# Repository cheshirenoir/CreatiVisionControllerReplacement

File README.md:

# CreatiVisionControllerReplacement

A bunch of PCBs designed to allow you to replace your failing CreatiVision controller membranes
The 4 sections are designed to be joined with short lengths of patch wire (ribbon cable).
See https://ilike8bits.com/total-joystick-madness/ for a build guide.

Notes: Use 0.6mm PCBs when yuou order. You'll need 3 different PCBs.

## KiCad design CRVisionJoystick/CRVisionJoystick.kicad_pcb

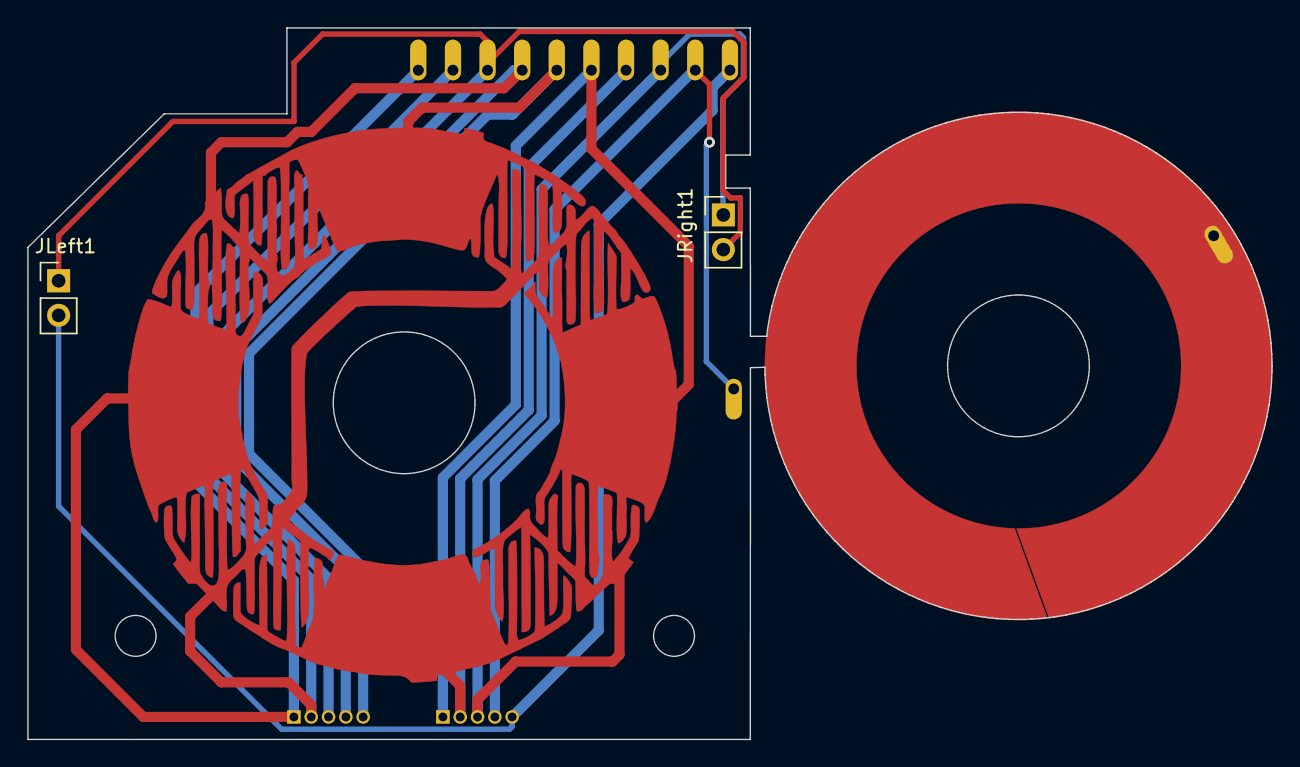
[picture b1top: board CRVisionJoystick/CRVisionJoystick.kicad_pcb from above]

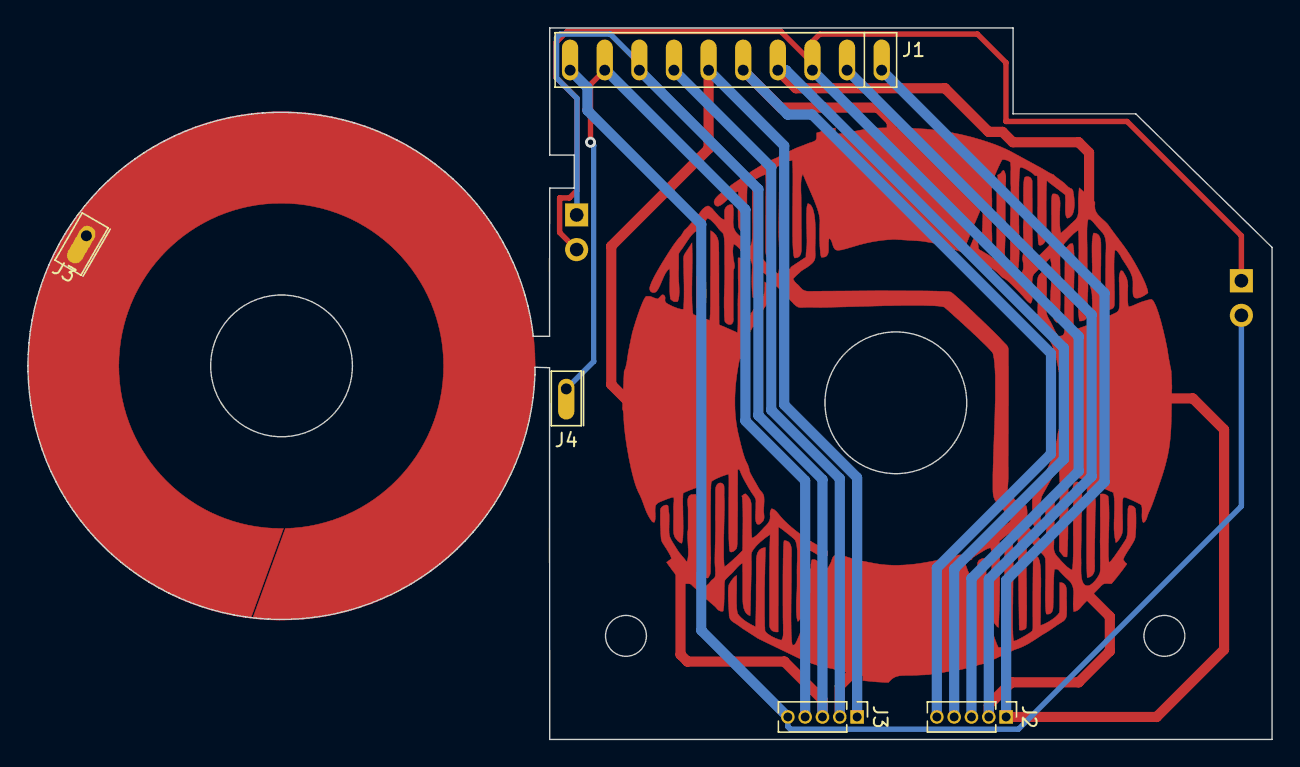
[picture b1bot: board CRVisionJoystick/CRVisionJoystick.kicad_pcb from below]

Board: 2 copper layers, 91.3 x 52.2 mm, 7 parts (5 on the bottom side), 10 nets.

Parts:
J1: Conn_01x10_Female; SIP-10L
J2, J3#2: Conn_01x05_Female; PinHeader_1x05_P1.27mm_Vertical
J3: Signal; SIP-1
J4: Conn_01x01_Female; SIP-1
JLeft1: Conn_01x02_Female; PinHeader_1x02_P2.54mm_Vertical
JRight1: Conn_01x02_Female; PinHeader_1x02_P2.54mm_Vertical

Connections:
unnamed: J1.1, J2.1, J3.1
unnamed: J1.2, J2.2
unnamed: J1.3, J2.3, JLeft1.1, JRight1.2
unnamed: J1.4, J2.4
unnamed: J1.5, J2.5
unnamed: J1.6, J3#2.1
unnamed: J1.7, J3#2.2
unnamed: J1.8, J3#2.3, JRight1.1
unnamed: J1.9, J3#2.4, J4.1
unnamed: J1.10, J3#2.5, JLeft1.2

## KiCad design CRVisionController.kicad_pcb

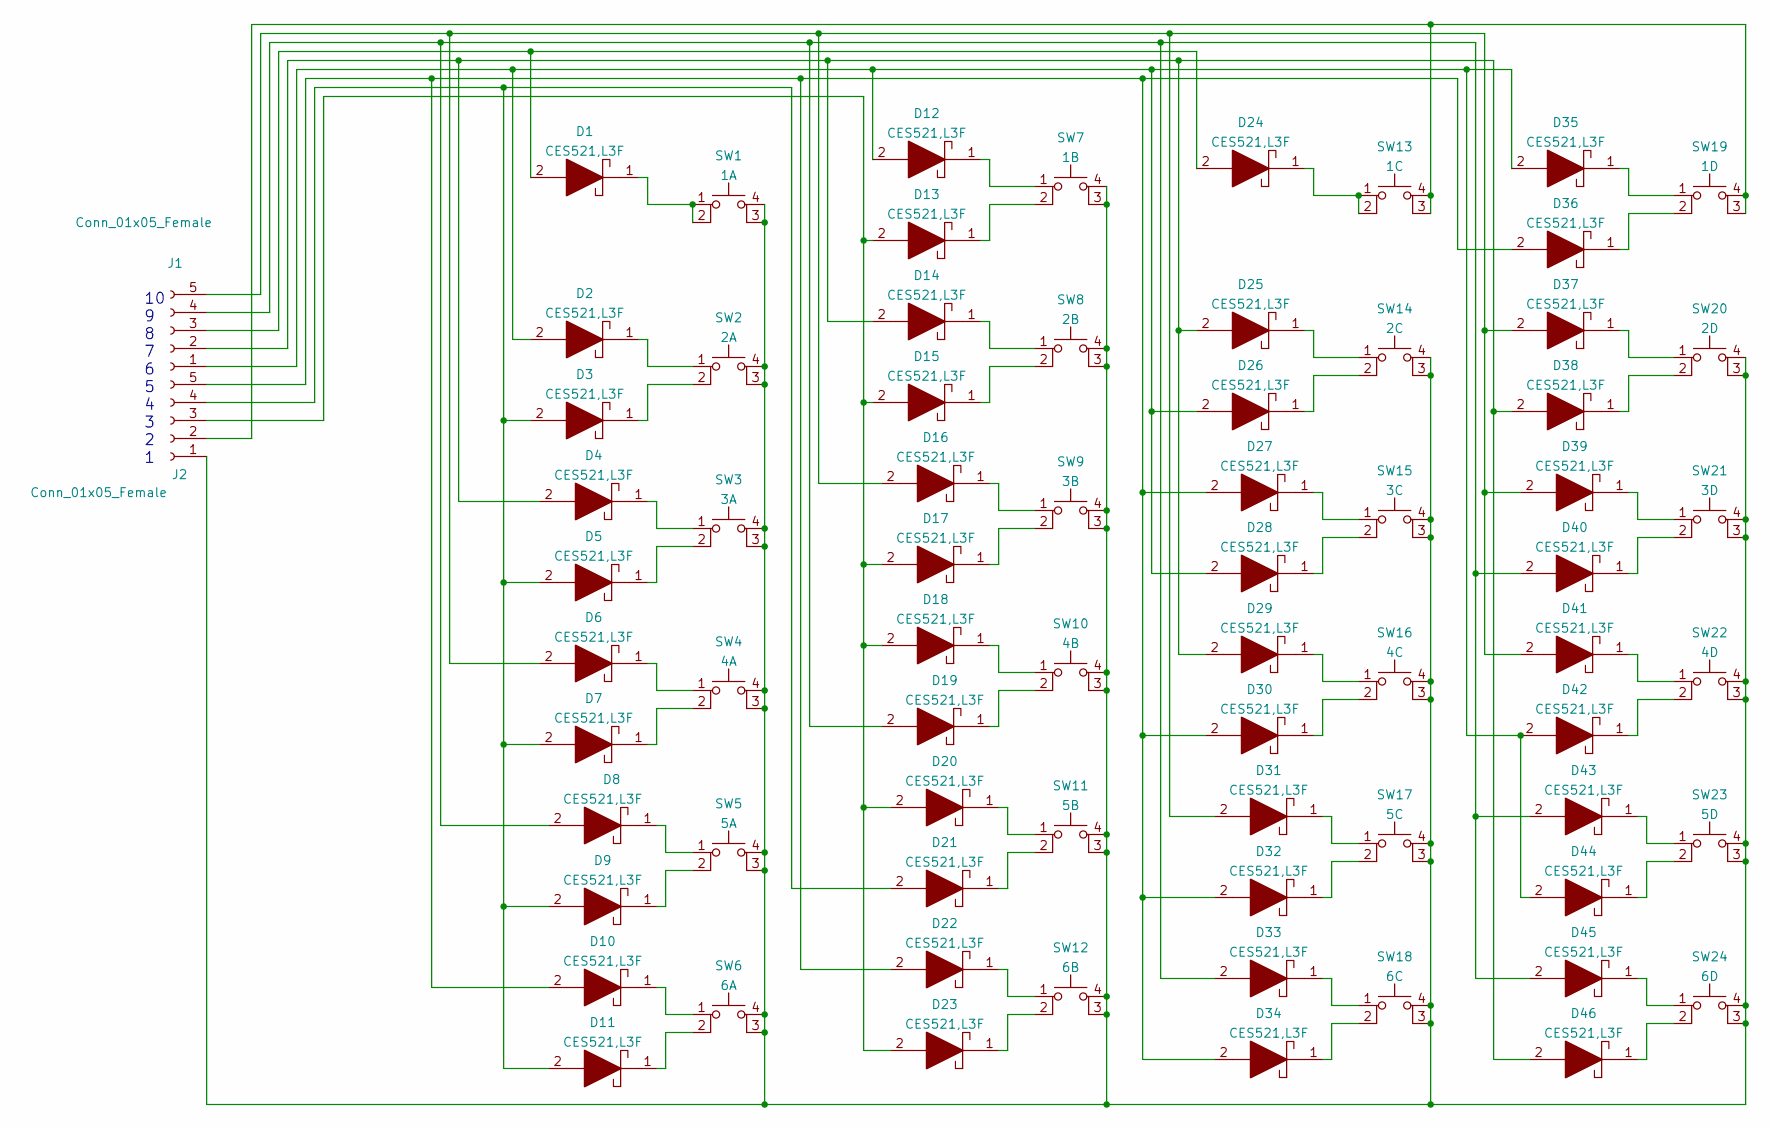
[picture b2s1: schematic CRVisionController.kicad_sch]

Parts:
D1, D2, D3, D4, D5, D6, D7, D8, D9, D10, D11, D12, D13, D14, D15, D16, D17, D18, D19, D20, D21, D22, D23, D24, D25, D26, D27, D28, D29, D30, D31, D32, D33, D34, D35, D36, D37, D38, D39, D40, D41, D42, D43, D44, D45, D46: CES521,L3F; D_SMA; Manufacturer_Part_Number CES521,L3F; Mouser Part Number 757-CES521L3F
J1, J2: Conn_01x05_Female; PinHeader_1x05_P1.27mm_Vertical
SW1: 1A; Jaycar SMD Tactical switch
SW2: 2A; Jaycar SMD Tactical switch
SW3: 3A; Jaycar SMD Tactical switch
SW4: 4A; Jaycar SMD Tactical switch
SW5: 5A; Jaycar SMD Tactical switch
SW6: 6A; Jaycar SMD Tactical switch
SW7: 1B; Jaycar SMD Tactical switch
SW8: 2B; Jaycar SMD Tactical switch
SW9: 3B; Jaycar SMD Tactical switch
SW10: 4B; Jaycar SMD Tactical switch
SW11: 5B; Jaycar SMD Tactical switch
SW12: 6B; Jaycar SMD Tactical switch
SW13: 1C; Jaycar SMD Tactical switch
SW14: 2C; Jaycar SMD Tactical switch
SW15: 3C; Jaycar SMD Tactical switch
SW16: 4C; Jaycar SMD Tactical switch
SW17: 5C; Jaycar SMD Tactical switch
SW18: 6C; Jaycar SMD Tactical switch
SW19: 1D; Jaycar SMD Tactical switch
SW20: 2D; Jaycar SMD Tactical switch
SW21: 3D; Jaycar SMD Tactical switch
SW22: 4D; Jaycar SMD Tactical switch
SW23: 5D; Jaycar SMD Tactical switch
SW24: 6D; Jaycar SMD Tactical switch

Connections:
unnamed 0: D1.1, SW1.1, SW1.2; also elsewhere on the board
unnamed: D1.2, D24.2, J1.3
unnamed: D2.1, SW2.1
unnamed: D3.1, SW2.2
unnamed: D4.1, SW3.1
unnamed: D5.1, SW3.2
unnamed: D6.1, SW4.1
unnamed: D7.1, SW4.2
unnamed: D8.1, SW5.1
unnamed: D9.1, SW5.2
unnamed: D10.1, SW6.1
unnamed: D10.2, D22.2, D27.2, D30.2, D32.2, D34.2, D36.2, J2.5
unnamed: D11.1, SW6.2
unnamed: D3.2, D5.2, D7.2, D9.2, D11.2, D21.2, J2.4
unnamed: D12.1, SW7.1
unnamed: D2.2, D12.2, D26.2, D28.2, D35.2, D42.2, D44.2, J1.1
unnamed: D13.1, SW7.2
unnamed: D13.2, D15.2, D17.2, D18.2, D20.2, D23.2, J2.3
unnamed: D14.1, SW8.1
unnamed: D4.2, D14.2, D25.2, D29.2, D38.2, D46.2, J1.2
unnamed: D15.1, SW8.2
unnamed: D16.1, SW9.1
unnamed: D6.2, D16.2, D31.2, D37.2, D39.2, D41.2, J1.5
unnamed: D17.1, SW9.2
unnamed: D18.1, SW10.1
unnamed: D19.1, SW10.2
unnamed: D8.2, D19.2, D33.2, D40.2, D43.2, D45.2, J1.4
unnamed: D20.1, SW11.1
unnamed: D21.1, SW11.2
unnamed: D22.1, SW12.1
unnamed: D23.1, SW12.2
unnamed: D24.1, SW13.1, SW13.2
unnamed: D25.1, SW14.1
unnamed: D26.1, SW14.2
unnamed: D27.1, SW15.1
unnamed: D28.1, SW15.2
unnamed: D29.1, SW16.1
unnamed: D30.1, SW16.2
unnamed: D31.1, SW17.1
unnamed: D32.1, SW17.2
unnamed: D33.1, SW18.1
unnamed: D34.1, SW18.2
unnamed: D35.1, SW19.1
unnamed: D36.1, SW19.2
unnamed: D37.1, SW20.1
unnamed: D38.1, SW20.2
unnamed: D39.1, SW21.1
unnamed: D40.1, SW21.2
unnamed: D41.1, SW22.1
unnamed: D42.1, SW22.2
unnamed: D43.1, SW23.1
unnamed: D44.1, SW23.2
unnamed: D45.1, SW24.1
unnamed: D46.1, SW24.2
unnamed 54: J2.1, SW1.3 (K), SW1.4 (A), SW2.3 (K), SW2.4 (A), SW3.3 (K), SW3.4 (A), SW4.3 (K), SW4.4 (A), SW5.3 (K), SW5.4 (A), SW6.3 (K), SW6.4 (A), SW7.3 (K), SW7.4 (A), SW8.3 (K), SW8.4 (A), SW9.3 (K), SW9.4 (A), SW10.3 (K), SW10.4 (A), SW11.3 (K), SW11.4 (A), SW12.3 (K), SW12.4 (A), SW14.3 (K), SW14.4 (A), SW15.3 (K), SW15.4 (A), SW16.3 (K), SW16.4 (A), SW17.3 (K), SW17.4 (A), SW18.3 (K), SW18.4 (A), SW20.3 (K), SW20.4 (A), SW21.3 (K), SW21.4 (A), SW22.3 (K), SW22.4 (A), SW23.3 (K), SW23.4 (A), SW24.3 (K), SW24.4 (A); also elsewhere on the board
unnamed: J2.2, SW13.3 (K), SW13.4 (A), SW19.3 (K), SW19.4 (A)

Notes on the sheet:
10 9 8 7 6 5 4 3 2 1

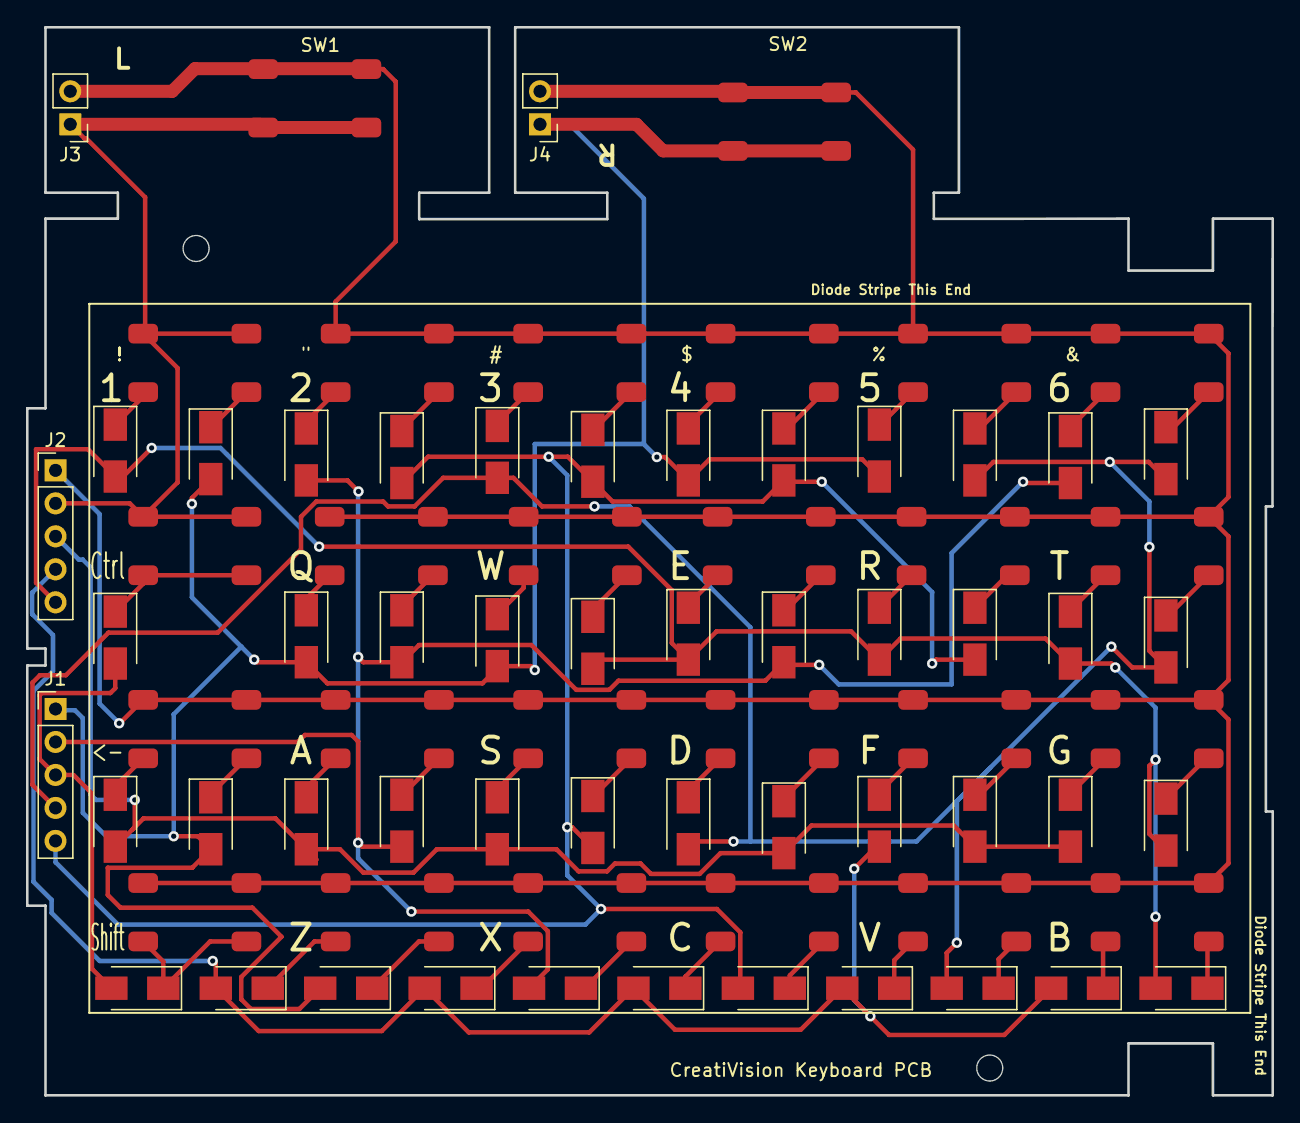
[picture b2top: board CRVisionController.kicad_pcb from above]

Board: 2 copper layers, 95.9 x 82.2 mm, 76 parts (0 on the bottom side), 56 nets.

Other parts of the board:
J3, J4: Conn_01x02_Female; PinHeader_1x02_P2.54mm_Vertical
SW1#2: 1A; Jaycar SMD Tactical switch
SW2#2: SW_MEC_5E; Jaycar SMD Tactical switch

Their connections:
unnamed 0: SW1#2.1, SW1#2.2; also elsewhere on the board
unnamed 54: SW1#2.3 (K), SW1#2.4 (A); also elsewhere on the board

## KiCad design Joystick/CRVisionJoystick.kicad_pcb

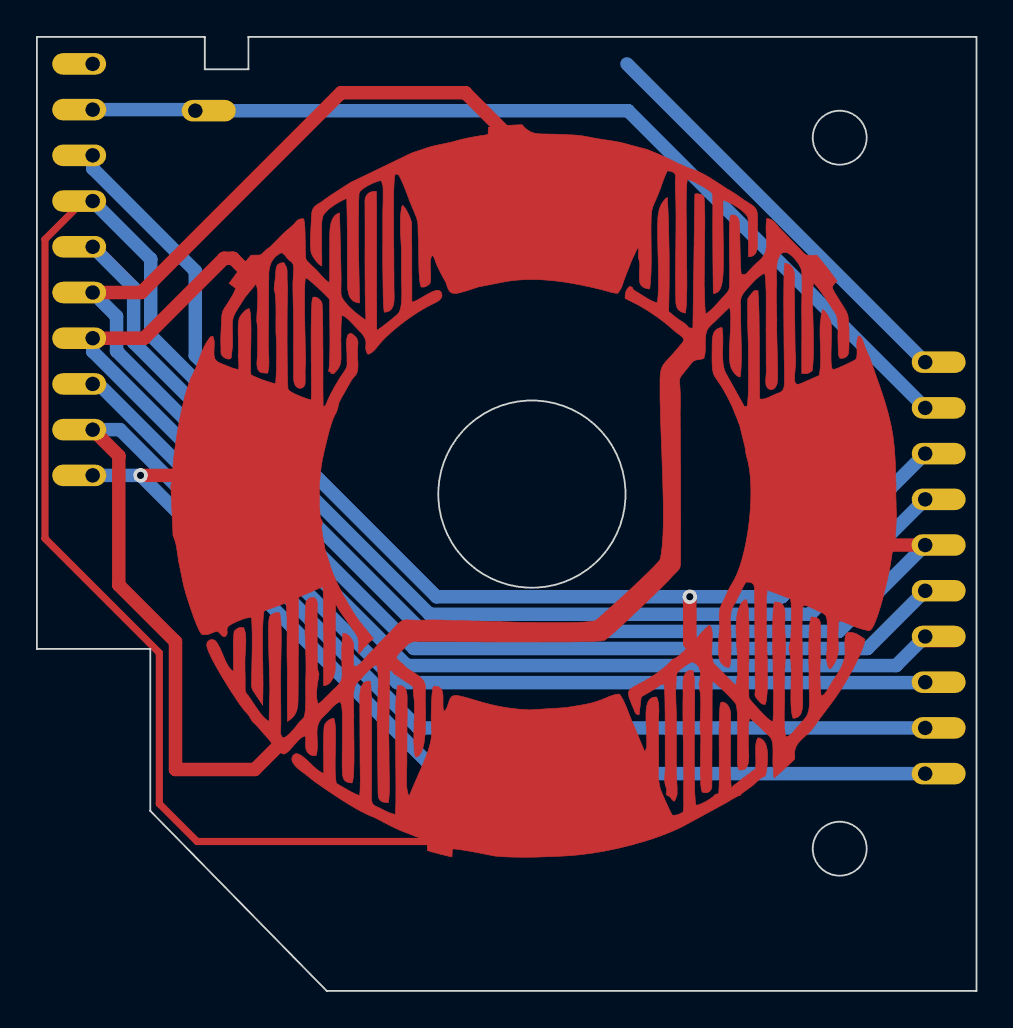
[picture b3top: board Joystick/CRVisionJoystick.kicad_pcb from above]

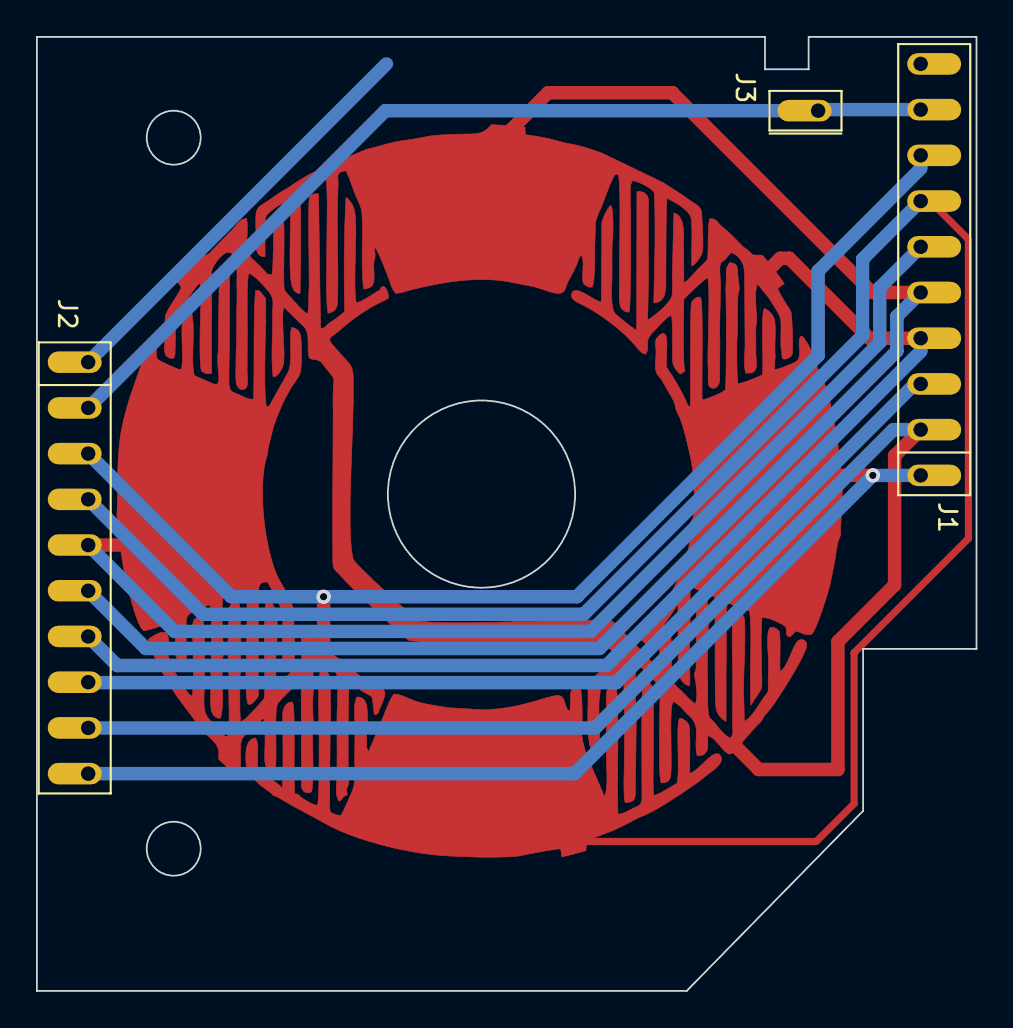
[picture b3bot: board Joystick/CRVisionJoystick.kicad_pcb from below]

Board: 2 copper layers, 52.2 x 53.0 mm, 3 parts (3 on the bottom side), 10 nets.

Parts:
J1: Conn_01x10_Female; SIP-10L
J2: Conn_01x10_Female; SIP-10R
J3: Signal; SIP-1

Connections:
unnamed: J1.1, J2.1
unnamed: J1.2, J2.2
unnamed: J1.3, J2.3
unnamed: J1.4, J2.4
unnamed: J1.5, J2.5
unnamed: J1.6, J2.6
unnamed: J1.7, J2.7
unnamed: J1.8, J2.8
unnamed: J1.9, J2.9, J3.1
unnamed: J1.10, J2.10

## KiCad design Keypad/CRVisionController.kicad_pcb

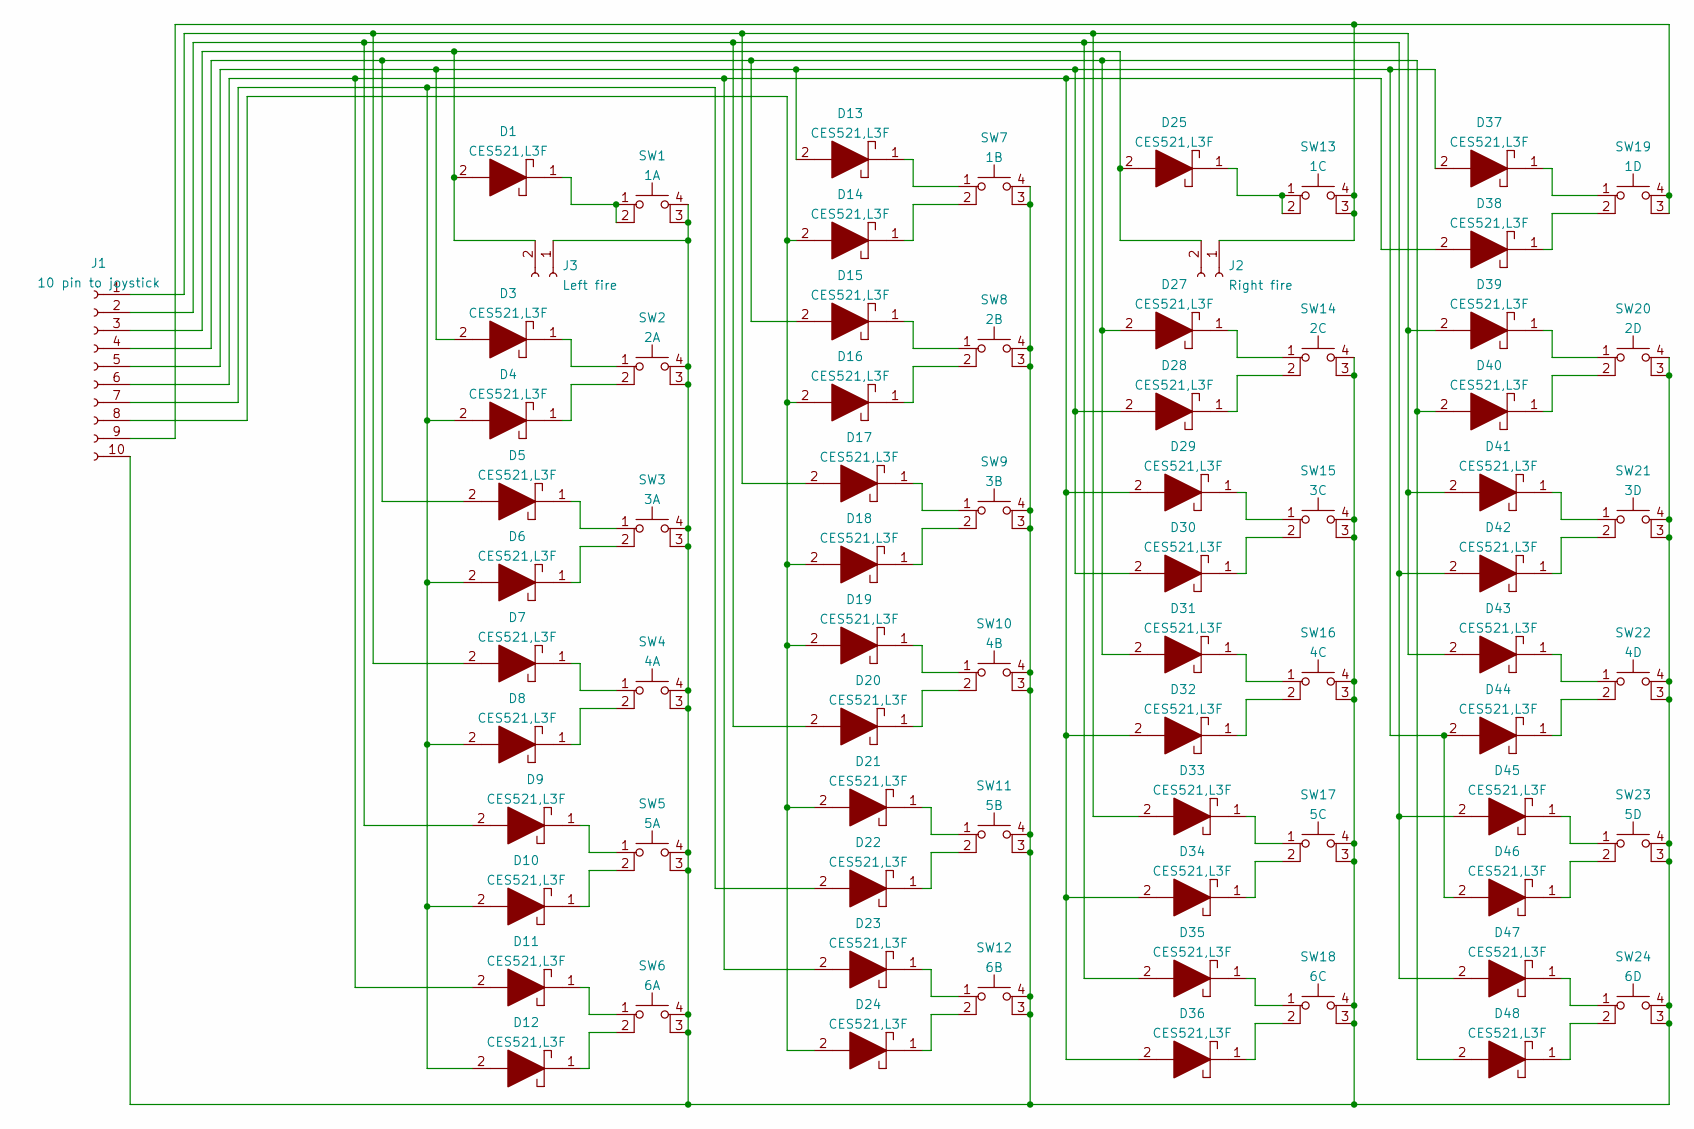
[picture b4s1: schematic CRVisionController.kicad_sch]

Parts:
D1, D3, D4, D5, D6, D7, D8, D9, D10, D11, D12, D13, D14, D15, D16, D17, D18, D19, D20, D21, D22, D23, D24, D25, D27, D28, D29, D30, D31, D32, D33, D34, D35, D36, D37, D38, D39, D40, D41, D42, D43, D44, D45, D46, D47, D48: CES521,L3F; D_SOD-523; Manufacturer_Part_Number CES521,L3F; Mouser Part Number 757-CES521L3F
J1: 10 pin to joystick; PinHeader_1x10_P2.54mm_Vertical
J2: Right fire; PinHeader_1x02_P2.54mm_Vertical
J3: Left fire; PinHeader_1x02_P2.54mm_Vertical
SW1: 1A; MicroTactile
SW2: 2A; MicroTactile
SW3: 3A; MicroTactile
SW4: 4A; MicroTactile
SW5: 5A; MicroTactile
SW6: 6A; MicroTactile
SW7: 1B; MicroTactile
SW8: 2B; MicroTactile
SW9: 3B; MicroTactile
SW10: 4B; MicroTactile
SW11: 5B; MicroTactile
SW12: 6B; MicroTactile
SW13: 1C; MicroTactile
SW14: 2C; MicroTactile
SW15: 3C; MicroTactile
SW16: 4C; MicroTactile
SW17: 5C; MicroTactile
SW18: 6C; MicroTactile
SW19: 1D; MicroTactile
SW20: 2D; MicroTactile
SW21: 3D; MicroTactile
SW22: 4D; MicroTactile
SW23: 5D; MicroTactile
SW24: 6D; MicroTactile

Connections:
unnamed: D1.1, SW1.1, SW1.2
unnamed: D1.2, D25.2, J1.3, J2.2, J3.2
unnamed: D3.1, SW2.1
unnamed: D4.1, SW2.2
unnamed: D5.1, SW3.1
unnamed: D6.1, SW3.2
unnamed: D7.1, SW4.1
unnamed: D8.1, SW4.2
unnamed: D9.1, SW5.1
unnamed: D10.1, SW5.2
unnamed: D4.2, D6.2, D8.2, D10.2, D12.2, D22.2, J1.7
unnamed: D11.1, SW6.1
unnamed: D11.2, D23.2, D29.2, D32.2, D34.2, D36.2, D38.2, J1.6
unnamed: D12.1, SW6.2
unnamed: D13.1, SW7.1
unnamed: D3.2, D13.2, D28.2, D30.2, D37.2, D44.2, D46.2, J1.5
unnamed: D14.1, SW7.2
unnamed: D14.2, D16.2, D18.2, D19.2, D21.2, D24.2, J1.8
unnamed: D15.1, SW8.1
unnamed: D5.2, D15.2, D27.2, D31.2, D40.2, D48.2, J1.4
unnamed: D16.1, SW8.2
unnamed: D17.1, SW9.1
unnamed: D7.2, D17.2, D33.2, D39.2, D41.2, D43.2, J1.1
unnamed: D18.1, SW9.2
unnamed: D19.1, SW10.1
unnamed: D20.1, SW10.2
unnamed: D9.2, D20.2, D35.2, D42.2, D45.2, D47.2, J1.2
unnamed: D21.1, SW11.1
unnamed: D22.1, SW11.2
unnamed: D23.1, SW12.1
unnamed: D24.1, SW12.2
unnamed: D25.1, SW13.1, SW13.2
unnamed: D27.1, SW14.1
unnamed: D28.1, SW14.2
unnamed: D29.1, SW15.1
unnamed: D30.1, SW15.2
unnamed: D31.1, SW16.1
unnamed: D32.1, SW16.2
unnamed: D33.1, SW17.1
unnamed: D34.1, SW17.2
unnamed: D35.1, SW18.1
unnamed: D36.1, SW18.2
unnamed: D37.1, SW19.1
unnamed: D38.1, SW19.2
unnamed: D39.1, SW20.1
unnamed: D40.1, SW20.2
unnamed: D41.1, SW21.1
unnamed: D42.1, SW21.2
unnamed: D43.1, SW22.1
unnamed: D44.1, SW22.2
unnamed: D45.1, SW23.1
unnamed: D46.1, SW23.2
unnamed: D47.1, SW24.1
unnamed: D48.1, SW24.2
unnamed: J1.9, J2.1, SW13.3 (K), SW13.4 (A), SW19.3 (K), SW19.4 (A)
unnamed: J1.10, J3.1, SW1.3 (K), SW1.4 (A), SW2.3 (K), SW2.4 (A), SW3.3 (K), SW3.4 (A), SW4.3 (K), SW4.4 (A), SW5.3 (K), SW5.4 (A), SW6.3 (K), SW6.4 (A), SW7.3 (K), SW7.4 (A), SW8.3 (K), SW8.4 (A), SW9.3 (K), SW9.4 (A), SW10.3 (K), SW10.4 (A), SW11.3 (K), SW11.4 (A), SW12.3 (K), SW12.4 (A), SW14.3 (K), SW14.4 (A), SW15.3 (K), SW15.4 (A), SW16.3 (K), SW16.4 (A), SW17.3 (K), SW17.4 (A), SW18.3 (K), SW18.4 (A), SW20.3 (K), SW20.4 (A), SW21.3 (K), SW21.4 (A), SW22.3 (K), SW22.4 (A), SW23.3 (K), SW23.4 (A), SW24.3 (K), SW24.4 (A)

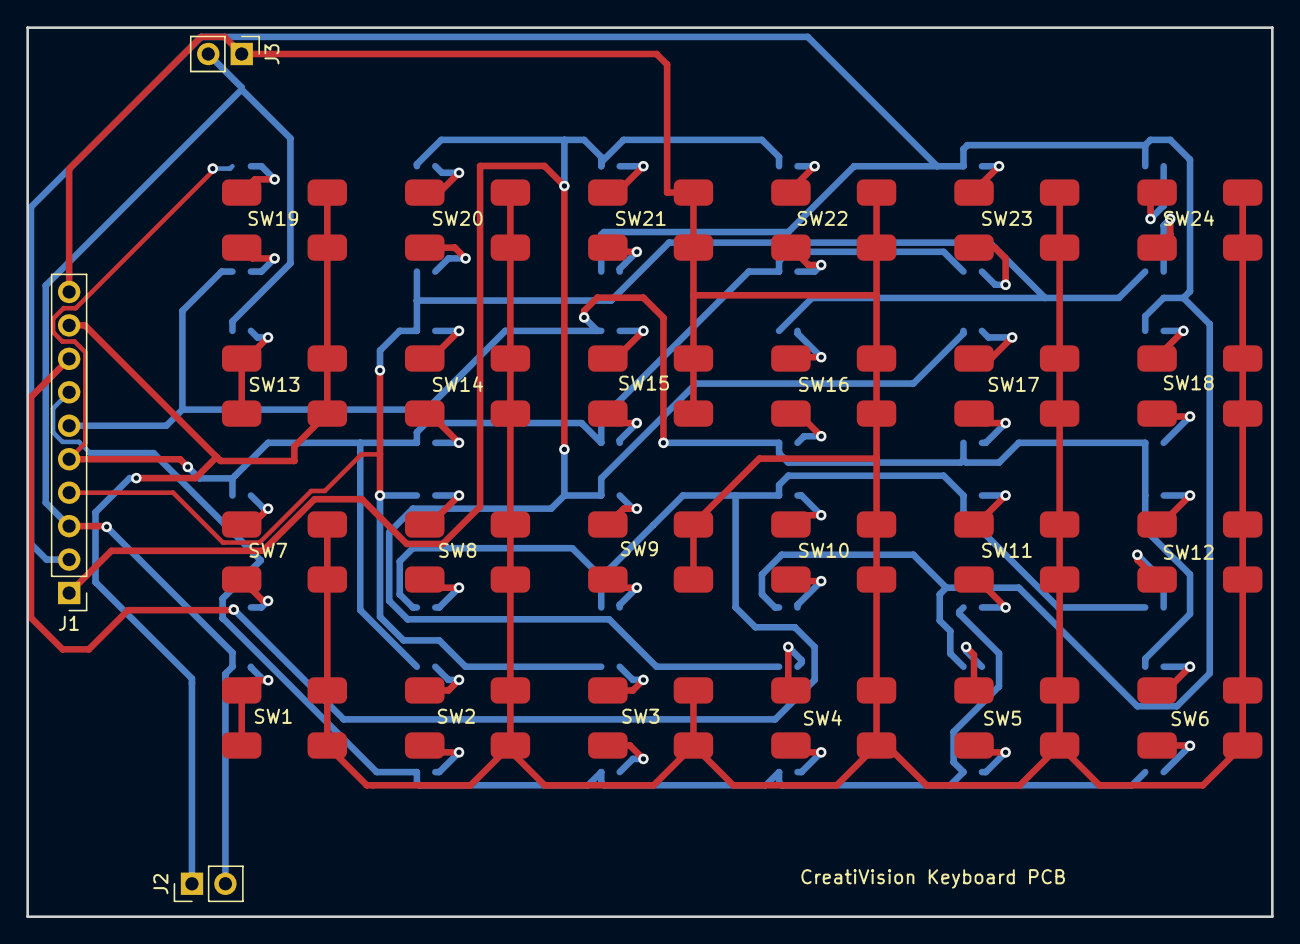
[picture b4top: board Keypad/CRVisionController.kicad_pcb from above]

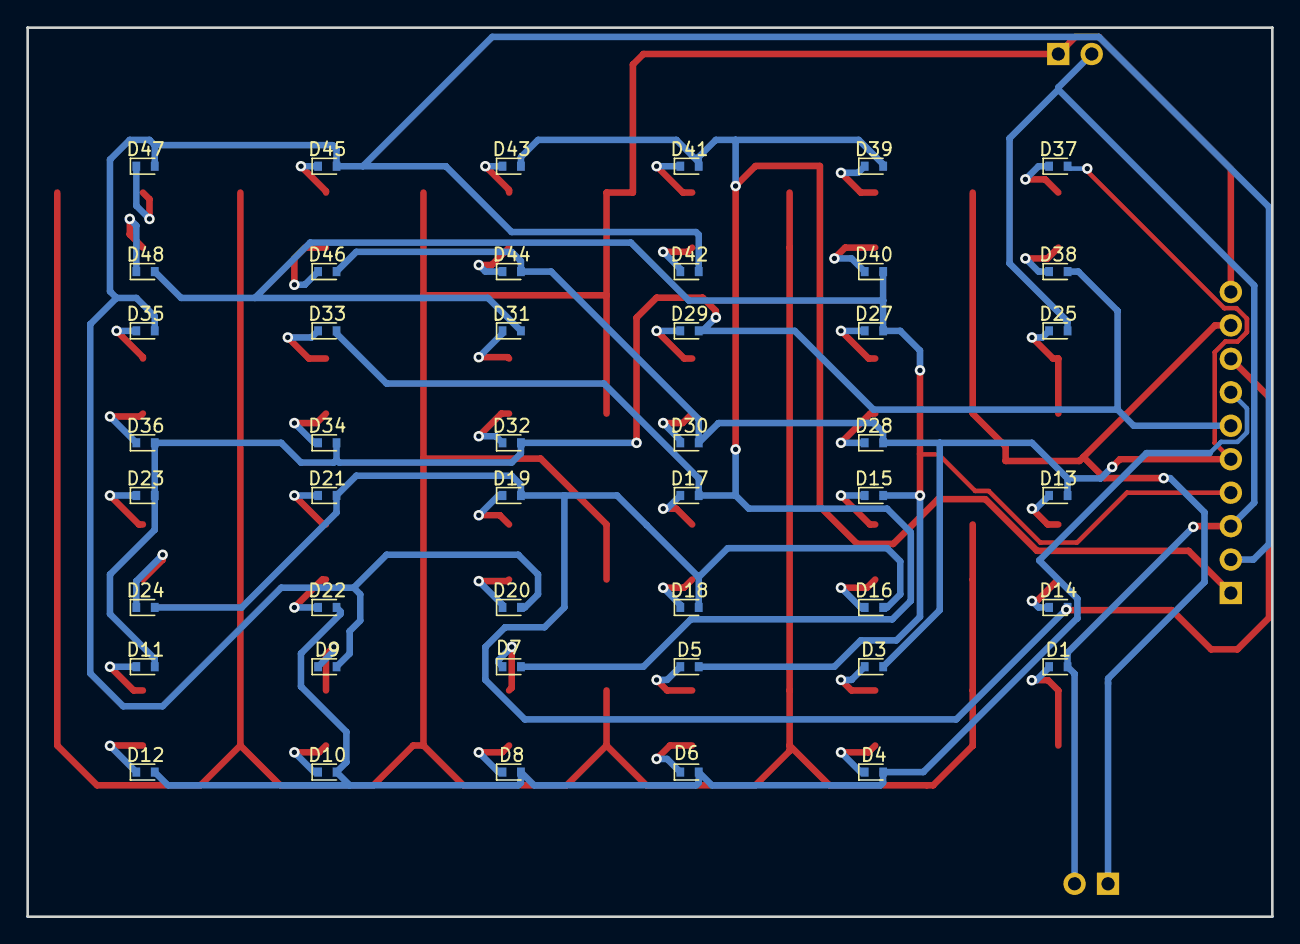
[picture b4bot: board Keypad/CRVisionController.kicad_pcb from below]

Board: 2 copper layers, 94.5 x 67.5 mm, 73 parts (46 on the bottom side), 56 nets.

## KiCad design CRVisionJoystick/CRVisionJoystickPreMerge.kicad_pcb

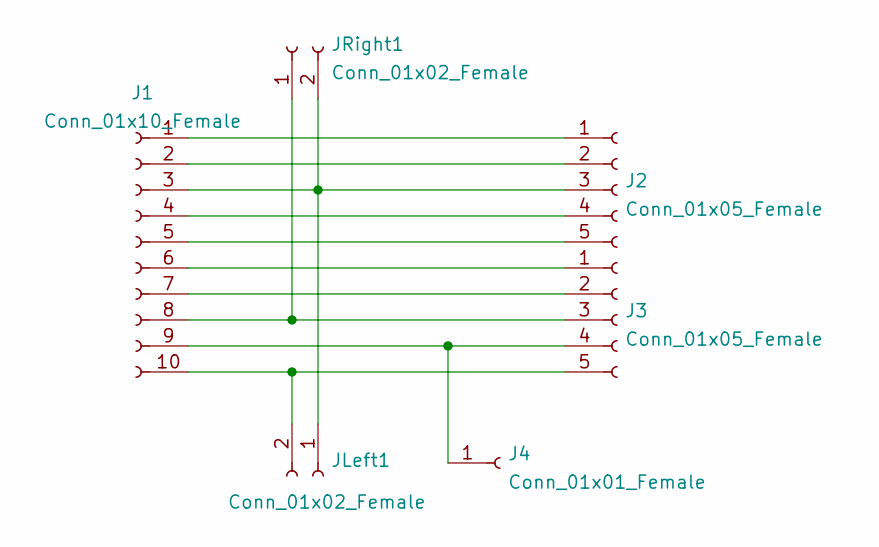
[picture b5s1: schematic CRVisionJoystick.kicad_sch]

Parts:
J1: Conn_01x10_Female; SIP-10L
J2, J3: Conn_01x05_Female; PinHeader_1x05_P1.27mm_Vertical
J4: Conn_01x01_Female; SIP-1
JLeft1: Conn_01x02_Female; PinHeader_1x02_P2.54mm_Vertical
JRight1: Conn_01x02_Female; PinHeader_1x02_P2.54mm_Vertical

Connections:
unnamed: J1.1, J2.1
unnamed: J1.2, J2.2
unnamed: J1.3, J2.3, JLeft1.1, JRight1.2
unnamed: J1.4, J2.4
unnamed: J1.5, J2.5
unnamed: J1.6, J3.1
unnamed: J1.7, J3.2
unnamed: J1.8, J3.3, JRight1.1
unnamed: J1.9, J3.4, J4.1
unnamed: J1.10, J3.5, JLeft1.2

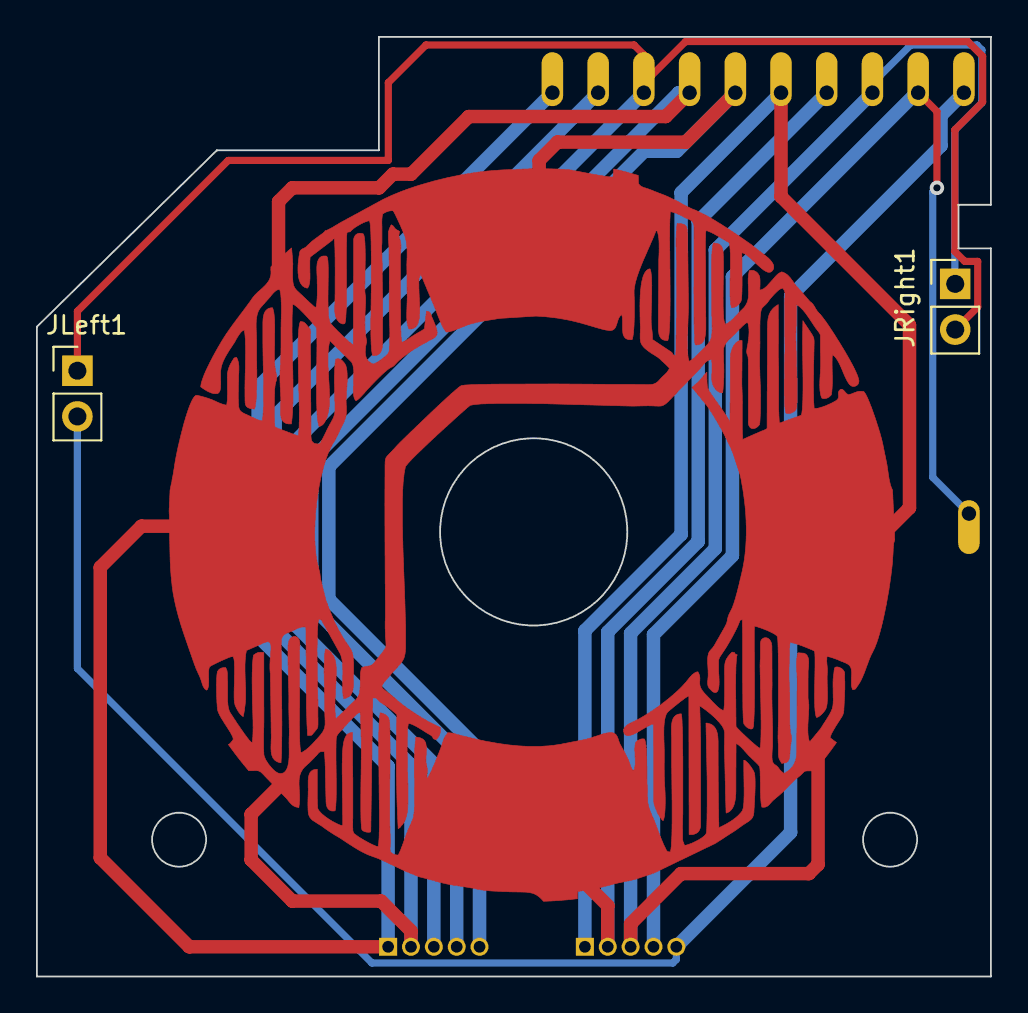
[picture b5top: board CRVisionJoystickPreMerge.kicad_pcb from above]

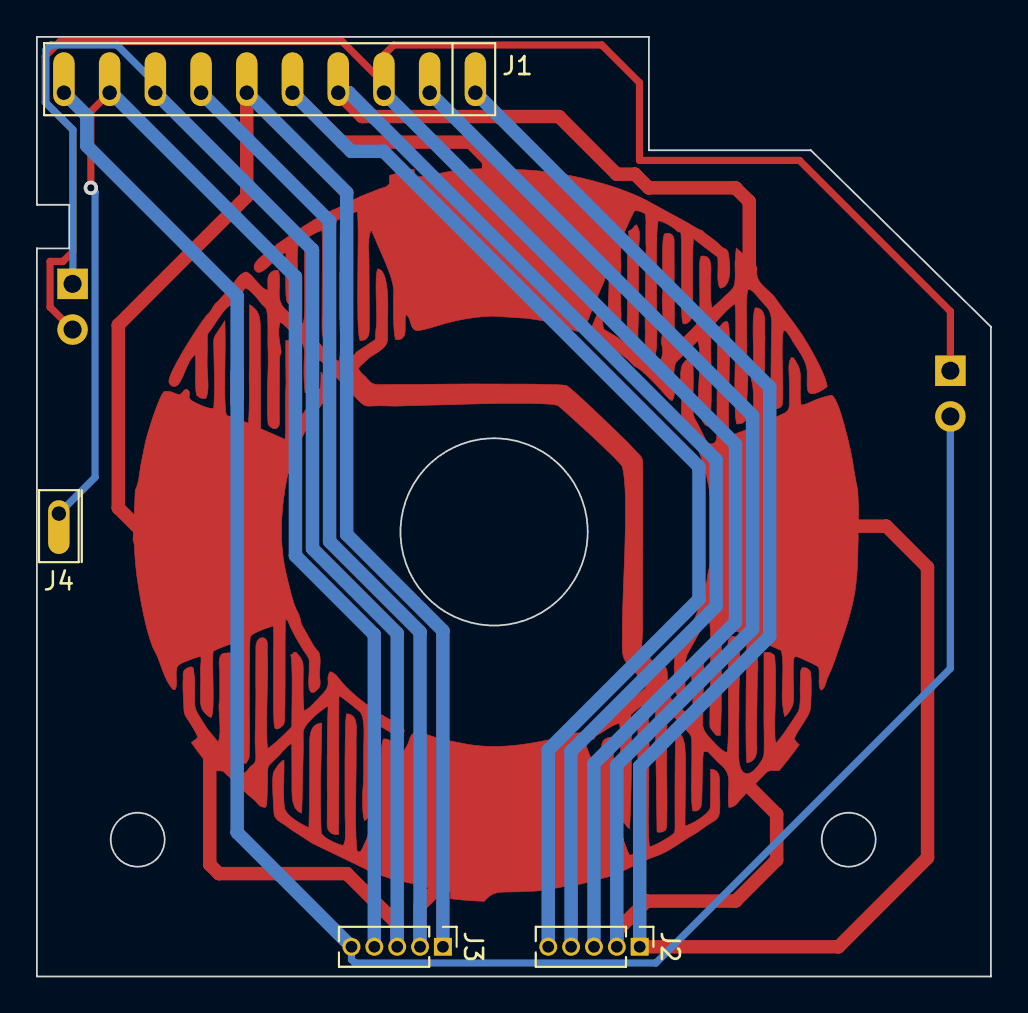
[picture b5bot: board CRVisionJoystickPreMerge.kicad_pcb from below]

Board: 2 copper layers, 53.0 x 52.2 mm, 6 parts (4 on the bottom side), 10 nets.

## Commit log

2022-07-24 Add files via upload
    Initial cut.
2022-08-10 Update README.md
    Updated status
2023-01-08 Add files via upload
    This is the working version, at last!
2023-01-08 Delete Keypad directory
    Stale files
2023-01-08 Delete Joystick directory
    Stale files
2023-01-08 Update README.md
    It works now
